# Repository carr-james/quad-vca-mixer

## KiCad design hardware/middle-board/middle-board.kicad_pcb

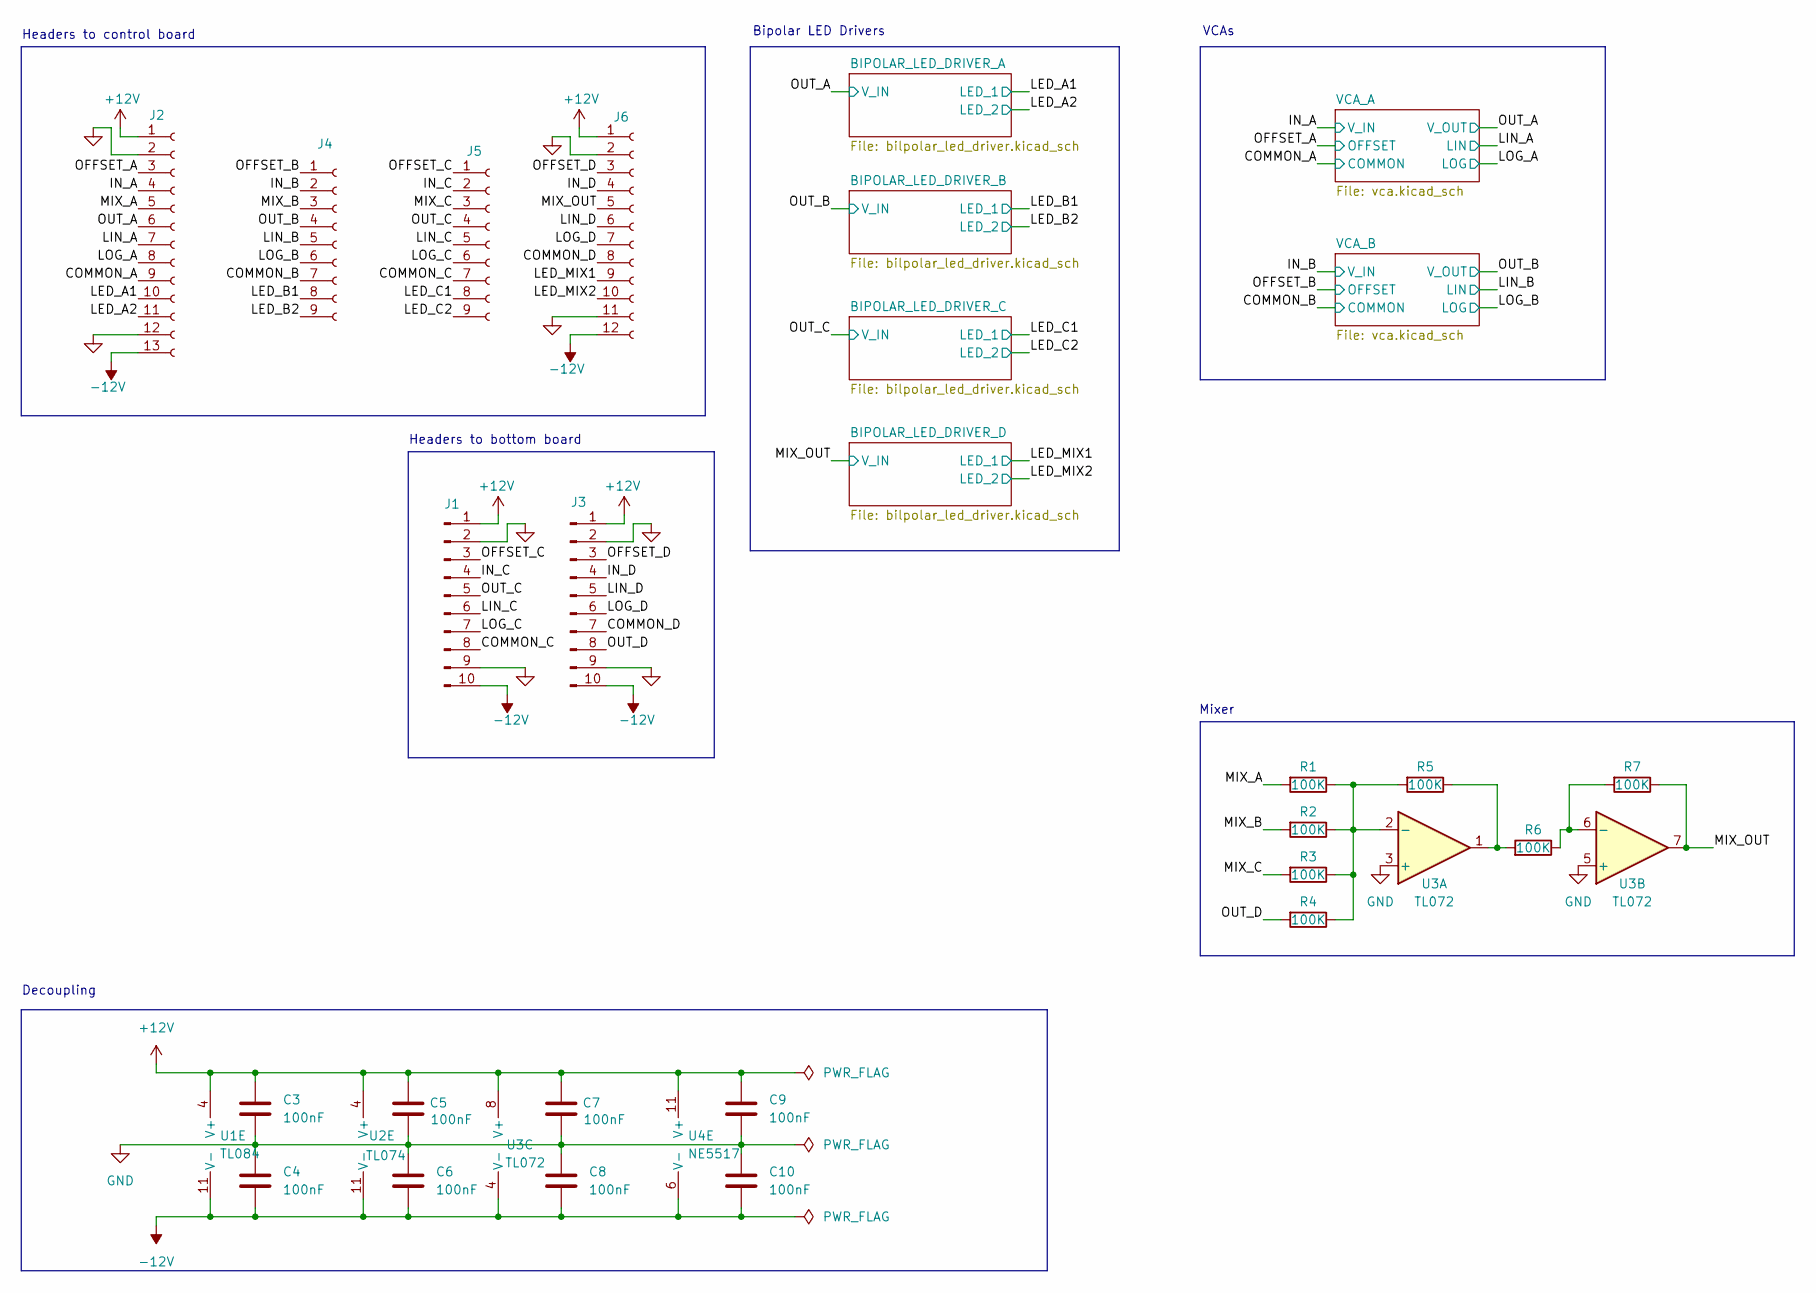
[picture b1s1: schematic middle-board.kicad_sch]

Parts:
C3, C4, C5, C6, C7, C8, C9, C10: 100nF; C_Disc_D3.4mm_W2.1mm_P2.50mm
J1, J3: 01x10 Male Pin Header; PinHeader_1x10_P2.54mm_Vertical
J2: 01x13 Female Pin Header; PinSocket_1x13_P2.54mm_Vertical
J4, J5: 01x09 Female Pin Header; PinSocket_1x09_P2.54mm_Vertical
J6: 01x12 Female Pin Header; PinSocket_1x12_P2.54mm_Vertical
R1, R2, R3, R4, R5, R6, R7: 100K; R_Axial_DIN0207_L6.3mm_D2.5mm_P7.62mm_Horizontal
U1: TL084; Texas_DYY0014A_TSOT-23-14_2x4.2mm_P0.5mm
U2: TL074; DIP-14_W7.62mm
U3: TL072; DIP-8_W7.62mm
U4: NE5517; SOIC-16_3.9x9.9mm_P1.27mm

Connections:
+12V: C3.1, C5.1, C7.1, C9.1, J1.1, J2.1, J3.1, J6.1, U1.4 (V+), U2.4 (V+), U3.8 (V+), U4.11 (V+); also elsewhere on the board
-12V: C4.2, C6.2, C8.2, C10.2, J1.10, J2.13, J3.10, J6.12, U1.11 (V-), U2.11 (V-), U3.4 (V-), U4.6 (V-); also elsewhere on the board
/COMMON_A: J2.9; also elsewhere on the board
/COMMON_B: J4.7, U4.16
/COMMON_C: J1.8, J5.7
/COMMON_D: J3.7, J6.8
/IN_A: J2.4; also elsewhere on the board
/IN_B: J4.2, U4.14 (+); also elsewhere on the board
/IN_C: J1.4, J5.2
/IN_D: J3.4, J6.4
/LED_A1: J2.10, U2.2 (-); also elsewhere on the board
/LED_A2: J2.11, U2.1; also elsewhere on the board
/LED_B1: J4.8, U2.6 (-); also elsewhere on the board
/LED_B2: J4.9, U2.7; also elsewhere on the board
/LED_C1: J5.8; also elsewhere on the board
/LED_C2: J5.9; also elsewhere on the board
/LED_MIX1: J6.9, U2.13 (-); also elsewhere on the board
/LED_MIX2: J6.10, U2.14; also elsewhere on the board
/LIN_A: J2.7; also elsewhere on the board
/LIN_B: J4.5; also elsewhere on the board
/LIN_C: J1.6, J5.5
/LIN_D: J3.5, J6.6
/LOG_A: J2.8; also elsewhere on the board
/LOG_B: J4.6; also elsewhere on the board
/LOG_C: J1.7, J5.6
/LOG_D: J3.6, J6.7
/MIX_A: J2.5, R1.1
/MIX_B: J4.3, R2.1
/MIX_C: J5.3, R3.1
/MIX_OUT: J6.5, R7.2, U2.12 (+), U3.7; also elsewhere on the board
/OFFSET_A: J2.3; also elsewhere on the board
/OFFSET_B: J4.1, U1.9 (-); also elsewhere on the board
/OFFSET_C: J1.3, J5.1
/OFFSET_D: J3.3, J6.3
/OUT_A: J2.6, U2.3 (+); also elsewhere on the board
/OUT_B: J4.4, U2.5 (+), U4.9; also elsewhere on the board
/OUT_C: J1.5, J5.4; also elsewhere on the board
/OUT_D: J3.8, R4.1
GND: C3.2, C4.1, C5.2, C6.1, C7.2, C8.1, C9.2, C10.1, J1.2, J1.9, J2.2, J2.12, J3.2, J3.9, J6.2, J6.11, U3.3 (+), U3.5 (+), U4.13 (-); also elsewhere on the board
unnamed 44: U1.8; also elsewhere on the board
unnamed: R5.2, R6.1, U3.1
unnamed 51: U1.14; also elsewhere on the board
unnamed 53: U4.10, U4.12; also elsewhere on the board
unnamed 57: U1.10 (+); also elsewhere on the board
unnamed 58: U1.12 (+); also elsewhere on the board
unnamed 59: U1.13 (-); also elsewhere on the board
unnamed: R1.2, R2.2, R3.2, R4.2, R5.1, U3.2 (-)
unnamed: R6.2, R7.1, U3.6 (-)

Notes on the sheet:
VCAs
Mixer
Headers to bottom board
Bipolar LED Drivers
Decoupling
Headers to control board

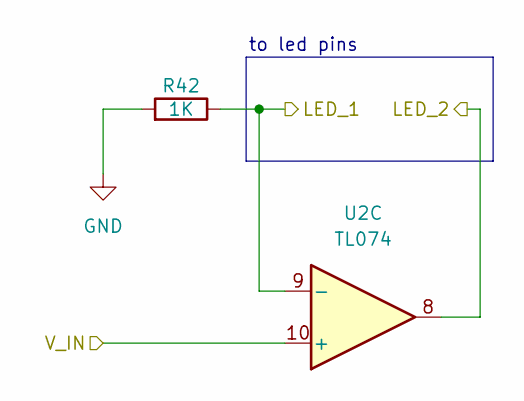
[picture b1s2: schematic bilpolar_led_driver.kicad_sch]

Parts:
R42: 1K; R_Axial_DIN0207_L6.3mm_D2.5mm_P7.62mm_Horizontal
U2: TL074; DIP-14_W7.62mm

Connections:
/LED_A1: U2.2 (-); also elsewhere on the board
/LED_A2: U2.1; also elsewhere on the board
/LED_B1: U2.6 (-); also elsewhere on the board
/LED_B2: U2.7; also elsewhere on the board
/LED_C1: R42.2, U2.9 (-); also elsewhere on the board
/LED_C2: U2.8; also elsewhere on the board
/LED_MIX1: U2.13 (-); also elsewhere on the board
/LED_MIX2: U2.14; also elsewhere on the board
/MIX_OUT: U2.12 (+); also elsewhere on the board
/OUT_A: U2.3 (+); also elsewhere on the board
/OUT_B: U2.5 (+); also elsewhere on the board
/OUT_C: U2.10 (+); also elsewhere on the board
GND: R42.1; also elsewhere on the board

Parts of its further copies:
R40, R41, R43: 1K; R_Axial_DIN0207_L6.3mm_D2.5mm_P7.62mm_Horizontal

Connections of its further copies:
/LED_A1: R40.2; also elsewhere on the board
/LED_B1: R41.2; also elsewhere on the board
/LED_MIX1: R43.2; also elsewhere on the board
GND: R40.1, R41.1, R43.1; also elsewhere on the board

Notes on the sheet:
to led pins

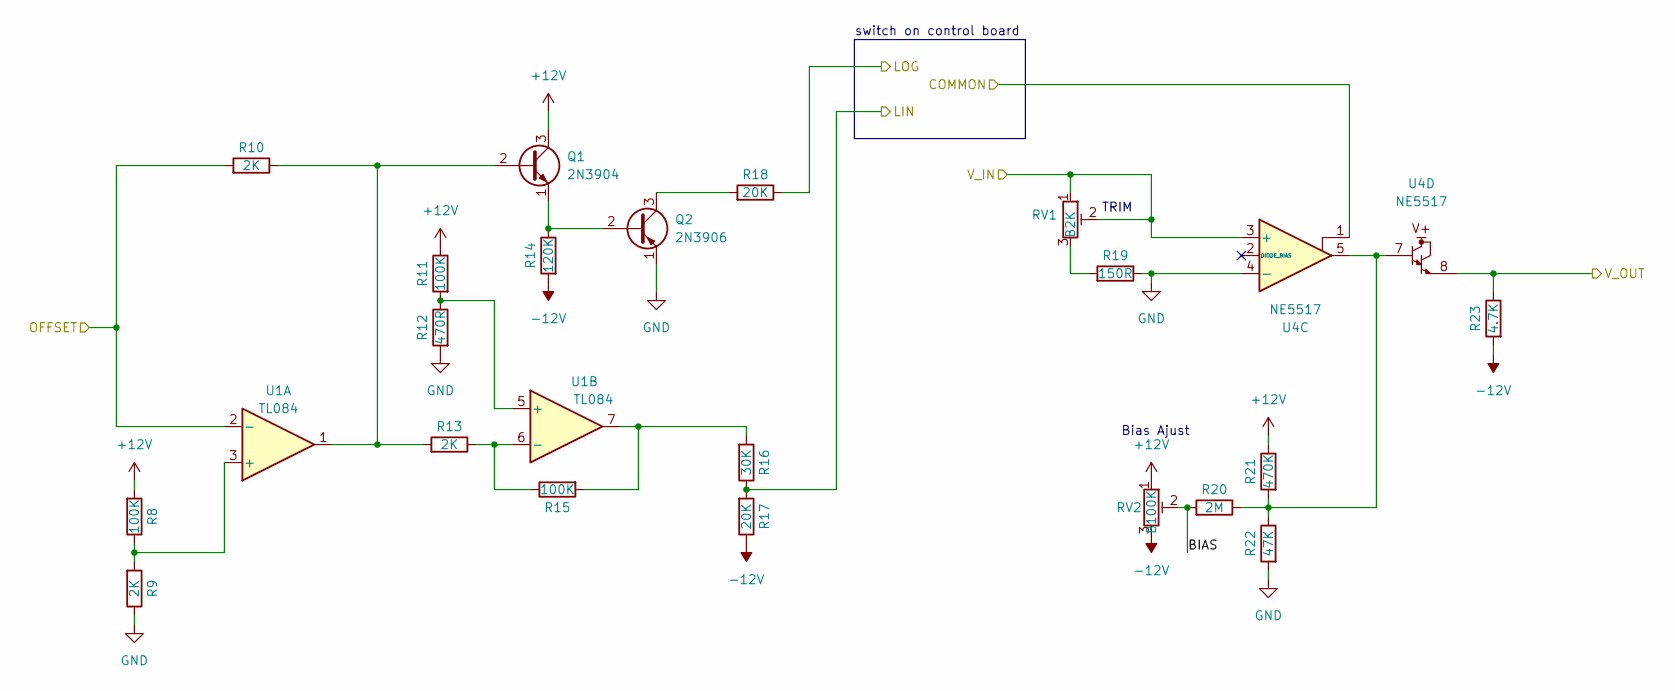
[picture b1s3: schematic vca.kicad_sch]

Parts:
Q1: 2N3904; TO-92_Inline
Q2: 2N3906; TO-92_Inline
R8, R11, R15: 100K; R_Axial_DIN0207_L6.3mm_D2.5mm_P7.62mm_Horizontal
R9, R10, R13: 2K; R_Axial_DIN0207_L6.3mm_D2.5mm_P7.62mm_Horizontal
R12: 470R; R_Axial_DIN0207_L6.3mm_D2.5mm_P7.62mm_Horizontal
R14: 120K; R_Axial_DIN0207_L6.3mm_D2.5mm_P7.62mm_Horizontal
R16: 30K; R_Axial_DIN0207_L6.3mm_D2.5mm_P7.62mm_Horizontal
R17, R18: 20K; R_Axial_DIN0207_L6.3mm_D2.5mm_P7.62mm_Horizontal
R19: 150R; R_Axial_DIN0207_L6.3mm_D2.5mm_P7.62mm_Horizontal
R20: 2M; R_Axial_DIN0207_L6.3mm_D2.5mm_P7.62mm_Horizontal
R21: 470K; R_Axial_DIN0207_L6.3mm_D2.5mm_P7.62mm_Horizontal
R22: 47K; R_Axial_DIN0207_L6.3mm_D2.5mm_P7.62mm_Horizontal
R23: 4.7K; R_Axial_DIN0207_L6.3mm_D2.5mm_P7.62mm_Horizontal
RV1: B2K; Potentiometer_Bourns_3296W_Horizontal
RV2: B100K; Potentiometer_Bourns_3296W_Horizontal
U1: TL084; Texas_DYY0014A_TSOT-23-14_2x4.2mm_P0.5mm
U4: NE5517; SOIC-16_3.9x9.9mm_P1.27mm

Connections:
+12V: Q1.3 (C), R8.1, R11.2, R21.2, RV2.1; also elsewhere on the board
-12V: R14.1, R17.2, R23.1, RV2.3; also elsewhere on the board
/COMMON_A: U4.1; also elsewhere on the board
/COMMON_B: U4.16; also elsewhere on the board
/IN_A: RV1.1, RV1.2, U4.3 (+); also elsewhere on the board
/IN_B: U4.14 (+); also elsewhere on the board
/LIN_A: R16.2, R17.1; also elsewhere on the board
/LOG_A: R18.2; also elsewhere on the board
/OFFSET_A: R10.1, U1.2 (-); also elsewhere on the board
/OFFSET_B: U1.9 (-); also elsewhere on the board
/OUT_A: R23.2, U4.8; also elsewhere on the board
/OUT_B: U4.9; also elsewhere on the board
/VCA_A/BIAS: R20.1, RV2.2
GND: Q2.1 (E), R9.2, R12.1, R19.2, R22.1, U4.4 (-), U4.13 (-); also elsewhere on the board
unnamed 41: Q1.2 (B), R10.2, R13.1, U1.1; also elsewhere on the board
unnamed: Q1.1 (E), Q2.2 (B), R14.2
unnamed: Q2.3 (C), R18.1
unnamed 44: U1.8; also elsewhere on the board
unnamed 48: R15.1, R16.1, U1.7; also elsewhere on the board
unnamed: R19.1, RV1.3
unnamed: R20.2, R21.1, R22.2, U4.5, U4.7
unnamed 51: U1.14; also elsewhere on the board
unnamed 53: U4.10, U4.12; also elsewhere on the board
unnamed 54: R8.2, R9.1, U1.3 (+); also elsewhere on the board
unnamed 55: R11.1, R12.2, U1.5 (+); also elsewhere on the board
unnamed 56: R13.2, R15.2, U1.6 (-); also elsewhere on the board
unnamed 57: U1.10 (+); also elsewhere on the board
unnamed 58: U1.12 (+); also elsewhere on the board
unnamed 59: U1.13 (-); also elsewhere on the board

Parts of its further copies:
Q3: 2N3904; TO-92_Inline
Q4: 2N3906; TO-92_Inline
R24, R27, R31: 100K; R_Axial_DIN0207_L6.3mm_D2.5mm_P7.62mm_Horizontal
R25, R26, R29: 2K; R_Axial_DIN0207_L6.3mm_D2.5mm_P7.62mm_Horizontal
R28: 470R; R_Axial_DIN0207_L6.3mm_D2.5mm_P7.62mm_Horizontal
R30: 120K; R_Axial_DIN0207_L6.3mm_D2.5mm_P7.62mm_Horizontal
R32: 30K; R_Axial_DIN0207_L6.3mm_D2.5mm_P7.62mm_Horizontal
R33, R34: 20K; R_Axial_DIN0207_L6.3mm_D2.5mm_P7.62mm_Horizontal
R35: 150R; R_Axial_DIN0207_L6.3mm_D2.5mm_P7.62mm_Horizontal
R36: 2M; R_Axial_DIN0207_L6.3mm_D2.5mm_P7.62mm_Horizontal
R37: 470K; R_Axial_DIN0207_L6.3mm_D2.5mm_P7.62mm_Horizontal
R38: 47K; R_Axial_DIN0207_L6.3mm_D2.5mm_P7.62mm_Horizontal
R39: 4.7K; R_Axial_DIN0207_L6.3mm_D2.5mm_P7.62mm_Horizontal
RV3: B2K; Potentiometer_Bourns_3296W_Horizontal
RV4: B100K; Potentiometer_Bourns_3296W_Horizontal

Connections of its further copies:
+12V: Q3.3 (C), R24.1, R27.2, R37.2, RV4.1; also elsewhere on the board
-12V: R30.1, R33.2, R39.1, RV4.3; also elsewhere on the board
/IN_B: RV3.1, RV3.2; also elsewhere on the board
/LIN_B: R32.2, R33.1; also elsewhere on the board
/LOG_B: R34.2; also elsewhere on the board
/OFFSET_B: R26.1; also elsewhere on the board
/OUT_B: R39.2; also elsewhere on the board
/VCA_B/BIAS: R36.1, RV4.2
GND: Q4.1 (E), R25.2, R28.1, R35.2, R38.1; also elsewhere on the board
unnamed 44: Q3.2 (B), R26.2, R29.1; also elsewhere on the board
unnamed: Q3.1 (E), Q4.2 (B), R30.2
unnamed: Q4.3 (C), R34.1
unnamed 51: R31.1, R32.1; also elsewhere on the board
unnamed: R35.1, RV3.3
unnamed 53: R36.2, R37.1, R38.2; also elsewhere on the board
unnamed 57: R24.2, R25.1; also elsewhere on the board
unnamed 58: R27.1, R28.2; also elsewhere on the board
unnamed 59: R29.2, R31.2; also elsewhere on the board

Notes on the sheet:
switch on control board
TRIM
Bias Ajust

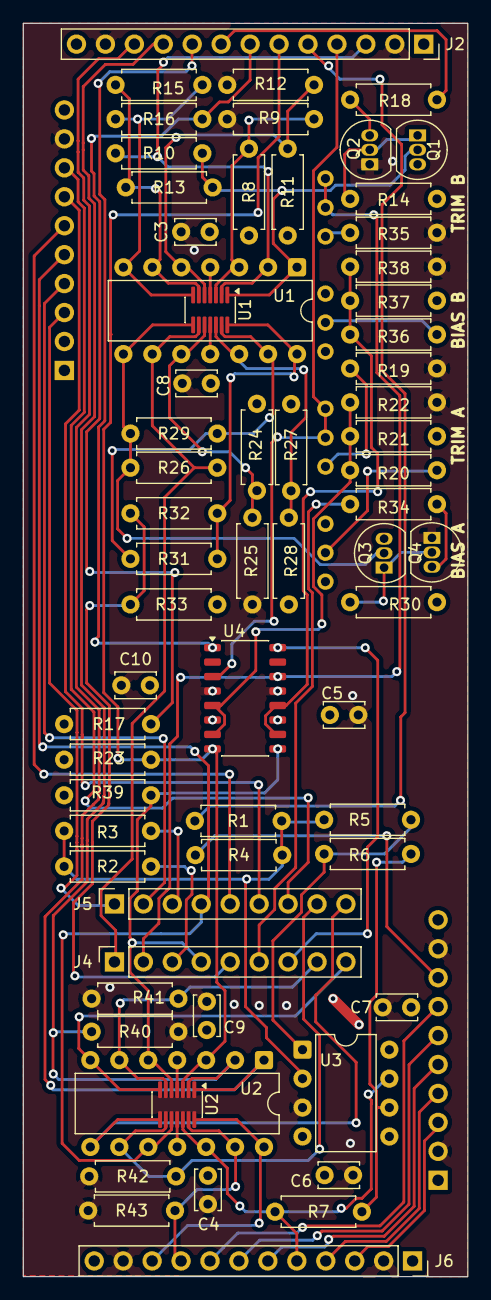
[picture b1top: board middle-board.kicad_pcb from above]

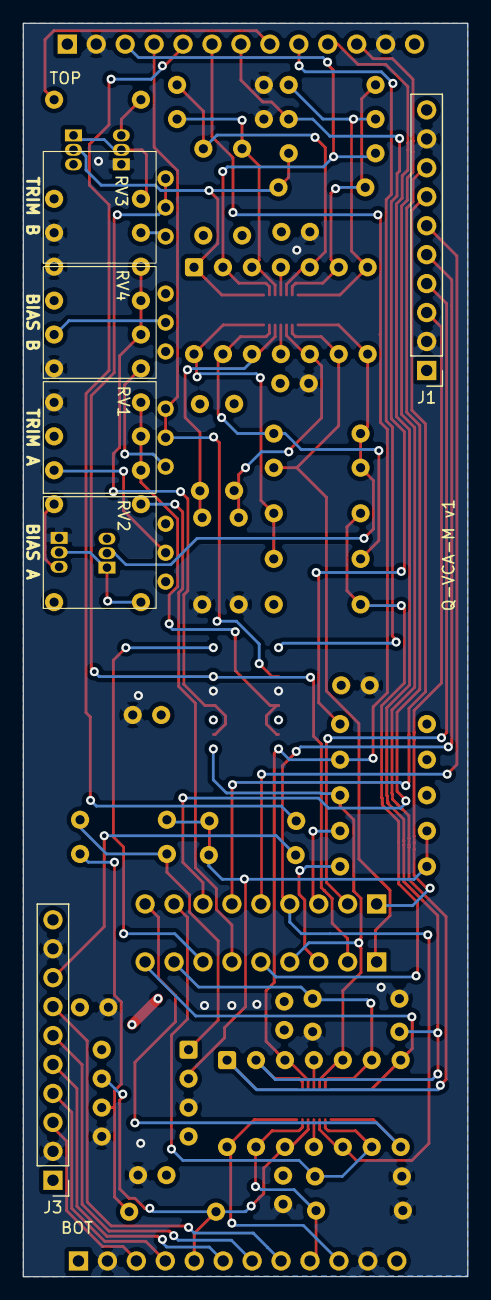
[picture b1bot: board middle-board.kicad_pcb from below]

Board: 4 copper layers, 39.0 x 110.0 mm, 71 parts (6 on the bottom side), 62 nets.

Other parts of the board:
U1#2: TL084; DIP-14_W7.62mm
U2#2: TL074; Texas_DYY0014A_TSOT-23-14_2x4.2mm_P0.5mm

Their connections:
+12V: U1#2.4 (V+), U2#2.4 (V+); also elsewhere on the board
-12V: U1#2.11 (V-), U2#2.11 (V-); also elsewhere on the board
/LED_A1: U2#2.2 (-); also elsewhere on the board
/LED_A2: U2#2.1; also elsewhere on the board
/LED_B1: U2#2.6 (-); also elsewhere on the board
/LED_B2: U2#2.7; also elsewhere on the board
/LED_C1: U2#2.9 (-); also elsewhere on the board
/LED_C2: U2#2.8; also elsewhere on the board
/LED_MIX1: U2#2.13 (-); also elsewhere on the board
/LED_MIX2: U2#2.14; also elsewhere on the board
/MIX_OUT: U2#2.12 (+); also elsewhere on the board
/OFFSET_A: U1#2.2 (-); also elsewhere on the board
/OFFSET_B: U1#2.9 (-); also elsewhere on the board
/OUT_A: U2#2.3 (+); also elsewhere on the board
/OUT_B: U2#2.5 (+); also elsewhere on the board
/OUT_C: U2#2.10 (+); also elsewhere on the board
unnamed 41: U1#2.1; also elsewhere on the board
unnamed 44: U1#2.8; also elsewhere on the board
unnamed 48: U1#2.7; also elsewhere on the board
unnamed 51: U1#2.14; also elsewhere on the board
unnamed 54: U1#2.3 (+); also elsewhere on the board
unnamed 55: U1#2.5 (+); also elsewhere on the board
unnamed 56: U1#2.6 (-); also elsewhere on the board
unnamed 57: U1#2.10 (+); also elsewhere on the board
unnamed 58: U1#2.12 (+); also elsewhere on the board
unnamed 59: U1#2.13 (-); also elsewhere on the board

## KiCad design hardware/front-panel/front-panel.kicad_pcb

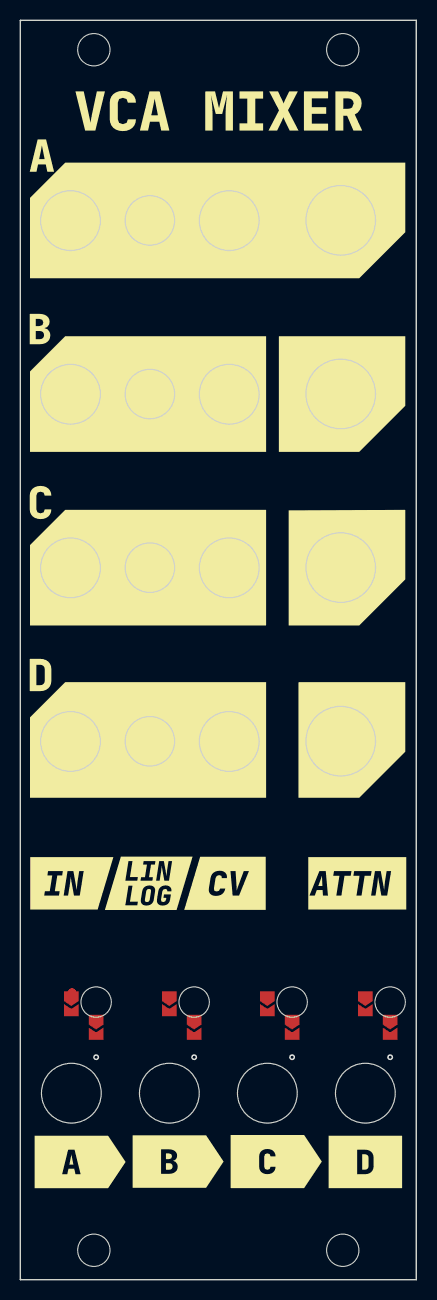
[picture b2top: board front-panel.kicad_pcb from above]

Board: 2 copper layers, 40.4 x 128.5 mm, 45 parts (0 on the bottom side), 4 nets.

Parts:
D1, D2, D3, D4: Bipolar LED; LED_D3.0mm_FP
J1, J2, J3, J4, J5, J6, J7, J8, J13, J14, J15, J16: Thonkicon; Thonkicon_FP
JP1, JP1#2, JP2, JP2#2, JP3, JP3#2, JP4, JP4#2: Jumper_2_Small_Bridged; SolderJumper-2_P1.3mm_Open_TrianglePad1.0x1.5mm
RV1, RV2, RV3, RV4: A100K; Alpha Potentiometer_FP
SW1, SW2, SW3, SW4: Subminiture SPDT; Sub-Miniature SPDT_FP
kibuzzard-690A2C8E: G***; kibuzzard-690A2C8E
kibuzzard-690A16BA: G***; kibuzzard-690A16BA
kibuzzard-690A26A7: G***; kibuzzard-690A26A7
kibuzzard-690A27E8: G***; kibuzzard-690A27E8
kibuzzard-690A27F2: G***; kibuzzard-690A27F2
kibuzzard-690A27FD: G***; kibuzzard-690A27FD
kibuzzard-690A058A: G***; kibuzzard-690A058A
kibuzzard-690A0571: G***; kibuzzard-690A0571
kibuzzard-690A0582: G***; kibuzzard-690A0582
kibuzzard-690A0592: G***; kibuzzard-690A0592
kibuzzard-690A1385: G***; kibuzzard-690A1385
kibuzzard-690A2811: G***; kibuzzard-690A2811
kibuzzard-69095FA6: G***; kibuzzard-69095FA6

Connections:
/DUMMY_NET_A: JP1.1 (A), JP1#2.1 (A)
/DUMMY_NET_B: JP2.1 (A), JP2#2.1 (A)
unnamed: JP1.2 (B), JP1#2.2 (B), JP3.1 (A), JP3#2.1 (A)
unnamed: JP2.2 (B), JP2#2.2 (B), JP4.1 (A), JP4#2.1 (A)

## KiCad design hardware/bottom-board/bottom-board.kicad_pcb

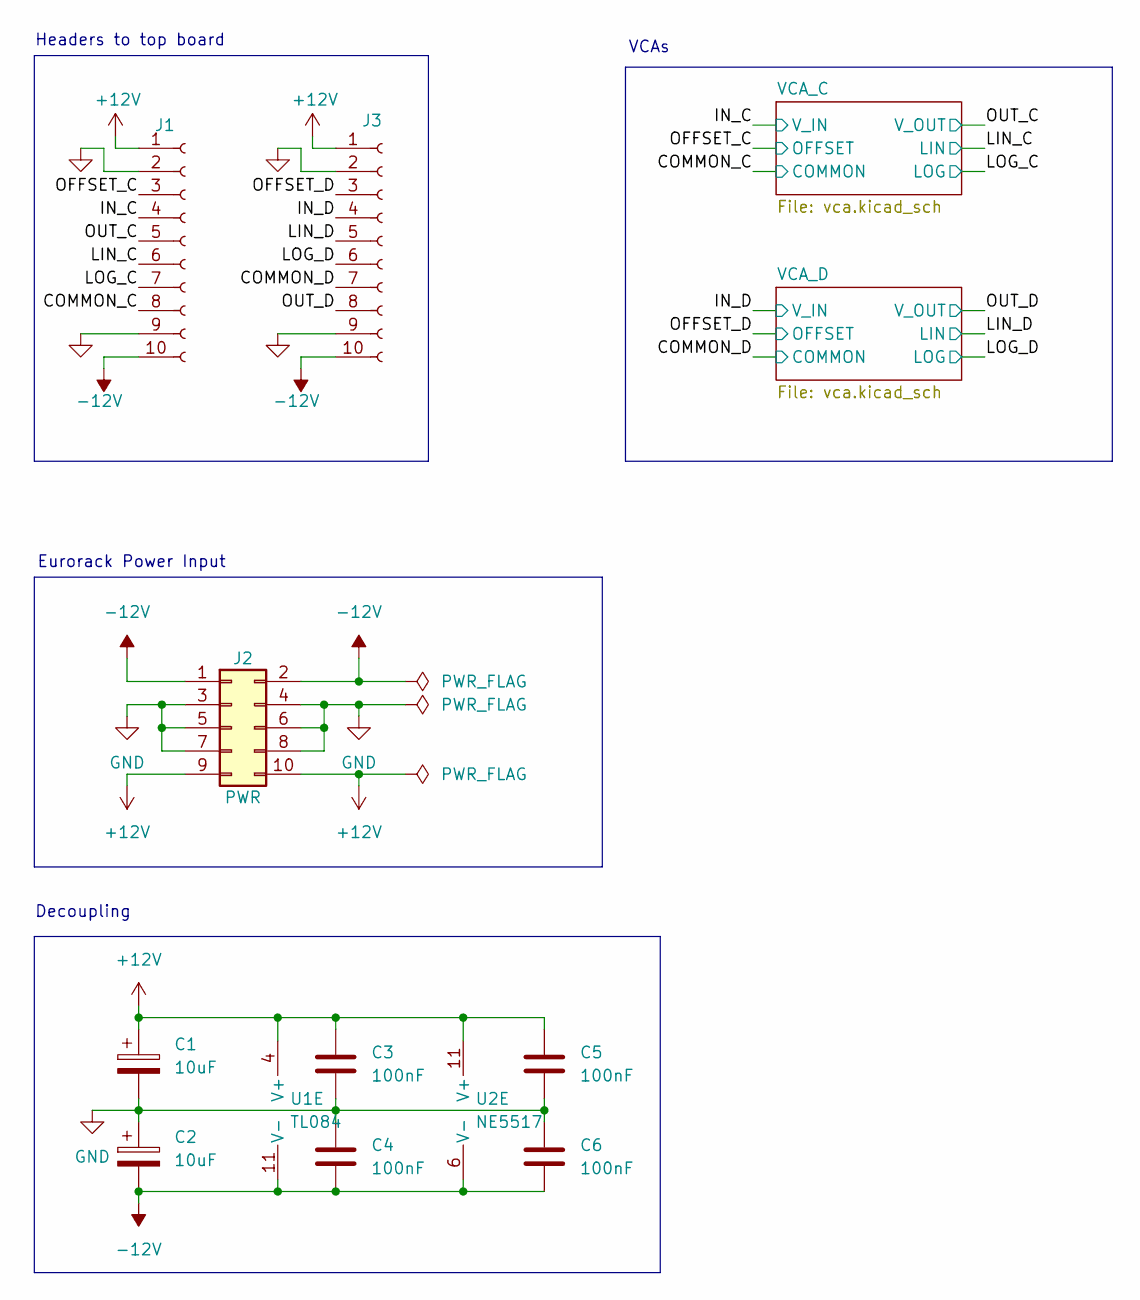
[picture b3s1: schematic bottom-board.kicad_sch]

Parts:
C1, C2: 10uF; CP_Radial_D5.0mm_H11.0mm_P2.00mm
C3, C4, C5, C6: 100nF; C_Disc_D3.4mm_W2.1mm_P2.50mm
J1, J3: 01x10 Female Pin Header; PinSocket_1x10_P2.54mm_Vertical
J2: PWR; Eurorack Power Header (10 pin)
U1: TL084; Texas_DYY0014A_TSOT-23-14_2x4.2mm_P0.5mm
U2: NE5517; SOIC-16_3.9x9.9mm_P1.27mm

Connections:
+12V: C1.1, C3.1, C5.1, J1.1, J2.9, J2.10, J3.1, U1.4 (V+), U2.11 (V+); also elsewhere on the board
-12V: C2.2, C4.2, C6.2, J1.10, J2.1, J2.2, J3.10, U1.11 (V-), U2.6 (V-); also elsewhere on the board
/COMMON_C: J1.8; also elsewhere on the board
/COMMON_D: J3.7, U2.1
/IN_C: J1.4; also elsewhere on the board
/IN_D: J3.4, U2.3 (+); also elsewhere on the board
/LIN_C: J1.6; also elsewhere on the board
/LIN_D: J3.5; also elsewhere on the board
/LOG_C: J1.7; also elsewhere on the board
/LOG_D: J3.6; also elsewhere on the board
/OFFSET_C: J1.3; also elsewhere on the board
/OFFSET_D: J3.3, U1.9 (-); also elsewhere on the board
/OUT_C: J1.5; also elsewhere on the board
/OUT_D: J3.8, U2.8; also elsewhere on the board
GND: C1.2, C2.1, C3.2, C4.1, C5.2, C6.1, J1.2, J1.9, J2.3, J2.4, J2.5, J2.6, J2.7, J2.8, J3.2, J3.9, U2.4 (-); also elsewhere on the board
unnamed 20: U1.8; also elsewhere on the board
unnamed 26: U1.14; also elsewhere on the board
unnamed 28: U2.5, U2.7; also elsewhere on the board
unnamed 32: U1.10 (+); also elsewhere on the board
unnamed 33: U1.12 (+); also elsewhere on the board
unnamed 34: U1.13 (-); also elsewhere on the board

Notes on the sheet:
Headers to top board
Eurorack Power Input
VCAs
Decoupling

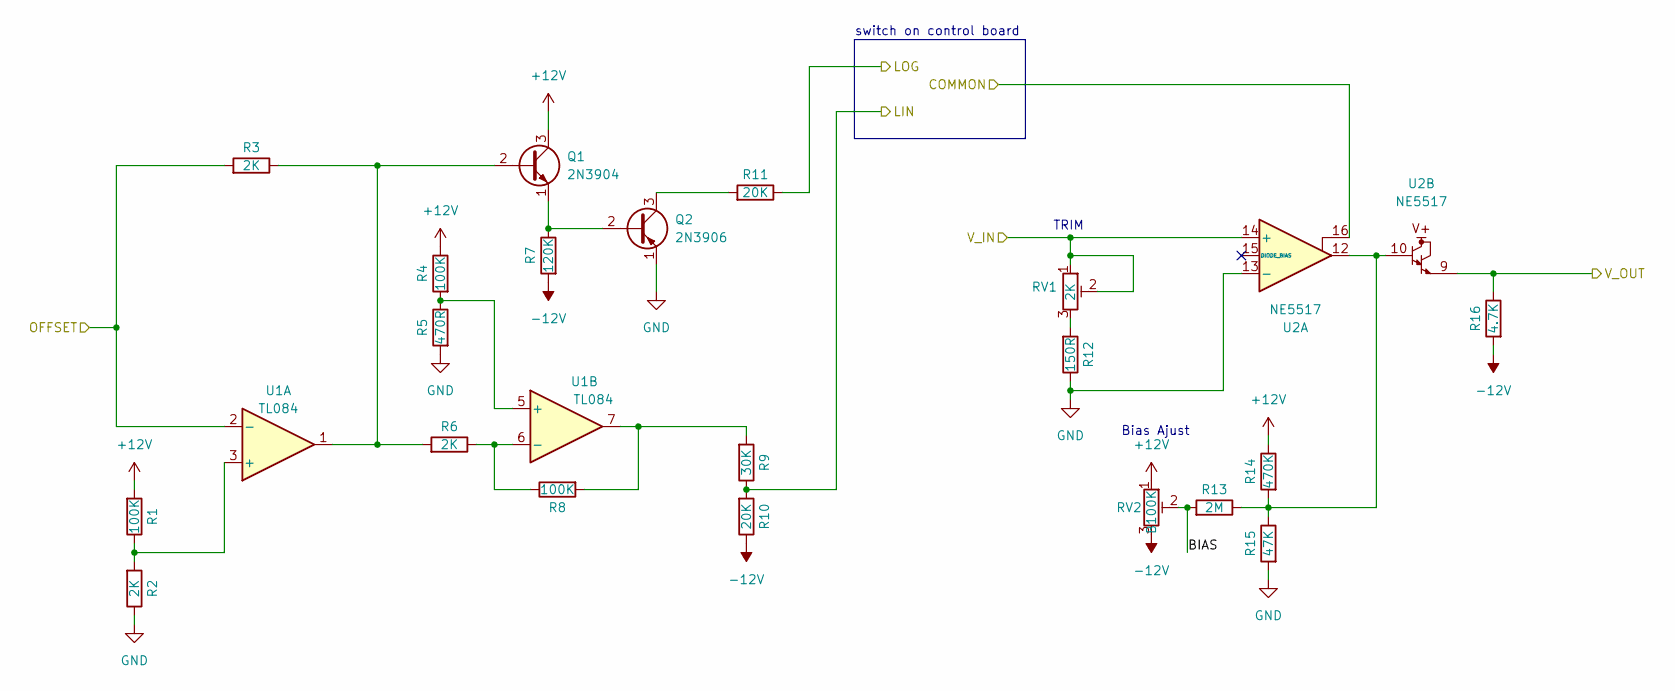
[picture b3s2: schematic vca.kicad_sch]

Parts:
Q1: 2N3904; TO-92_Inline
Q2: 2N3906; TO-92_Inline
R1, R4, R8: 100K; R_Axial_DIN0207_L6.3mm_D2.5mm_P7.62mm_Horizontal
R2, R3, R6: 2K; R_Axial_DIN0207_L6.3mm_D2.5mm_P7.62mm_Horizontal
R5: 470R; R_Axial_DIN0207_L6.3mm_D2.5mm_P7.62mm_Horizontal
R7: 120K; R_Axial_DIN0207_L6.3mm_D2.5mm_P7.62mm_Horizontal
R9: 30K; R_Axial_DIN0207_L6.3mm_D2.5mm_P7.62mm_Horizontal
R10, R11: 20K; R_Axial_DIN0207_L6.3mm_D2.5mm_P7.62mm_Horizontal
R12: 150R; R_Axial_DIN0207_L6.3mm_D2.5mm_P7.62mm_Horizontal
R13: 2M; R_Axial_DIN0207_L6.3mm_D2.5mm_P7.62mm_Horizontal
R14: 470K; R_Axial_DIN0207_L6.3mm_D2.5mm_P7.62mm_Horizontal
R15: 47K; R_Axial_DIN0207_L6.3mm_D2.5mm_P7.62mm_Horizontal
R16: 4.7K; R_Axial_DIN0207_L6.3mm_D2.5mm_P7.62mm_Horizontal
RV1: 2K; Potentiometer_Bourns_3296W_Horizontal
RV2: B100K; Potentiometer_Bourns_3296W_Horizontal
U1: TL084; Texas_DYY0014A_TSOT-23-14_2x4.2mm_P0.5mm
U2: NE5517; SOIC-16_3.9x9.9mm_P1.27mm

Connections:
+12V: Q1.3 (C), R1.1, R4.2, R14.2, RV2.1; also elsewhere on the board
-12V: R7.1, R10.2, R16.1, RV2.3; also elsewhere on the board
/COMMON_C: U2.16; also elsewhere on the board
/COMMON_D: U2.1; also elsewhere on the board
/IN_C: RV1.1, RV1.2, U2.14 (+); also elsewhere on the board
/IN_D: U2.3 (+); also elsewhere on the board
/LIN_C: R9.2, R10.1; also elsewhere on the board
/LOG_C: R11.2; also elsewhere on the board
/OFFSET_C: R3.1, U1.2 (-); also elsewhere on the board
/OFFSET_D: U1.9 (-); also elsewhere on the board
/OUT_C: R16.2, U2.9; also elsewhere on the board
/OUT_D: U2.8; also elsewhere on the board
/VCA_C/BIAS: R13.1, RV2.2
GND: Q2.1 (E), R2.2, R5.1, R12.2, R15.1, U2.4 (-), U2.13 (-); also elsewhere on the board
unnamed 17: Q1.2 (B), R3.2, R6.1, U1.1; also elsewhere on the board
unnamed: Q1.1 (E), Q2.2 (B), R7.2
unnamed: Q2.3 (C), R11.1
unnamed 20: U1.8; also elsewhere on the board
unnamed 23: R8.1, R9.1, U1.7; also elsewhere on the board
unnamed: R12.1, RV1.3
unnamed: R13.2, R14.1, R15.2, U2.10, U2.12
unnamed 26: U1.14; also elsewhere on the board
unnamed 28: U2.5, U2.7; also elsewhere on the board
unnamed 29: R1.2, R2.1, U1.3 (+); also elsewhere on the board
unnamed 30: R4.1, R5.2, U1.5 (+); also elsewhere on the board
unnamed 31: R6.2, R8.2, U1.6 (-); also elsewhere on the board
unnamed 32: U1.10 (+); also elsewhere on the board
unnamed 33: U1.12 (+); also elsewhere on the board
unnamed 34: U1.13 (-); also elsewhere on the board

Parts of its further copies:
Q3: 2N3904; TO-92_Inline
Q4: 2N3906; TO-92_Inline
R17, R20, R24: 100K; R_Axial_DIN0207_L6.3mm_D2.5mm_P7.62mm_Horizontal
R18, R19, R22: 2K; R_Axial_DIN0207_L6.3mm_D2.5mm_P7.62mm_Horizontal
R21: 470R; R_Axial_DIN0207_L6.3mm_D2.5mm_P7.62mm_Horizontal
R23: 120K; R_Axial_DIN0207_L6.3mm_D2.5mm_P7.62mm_Horizontal
R25: 30K; R_Axial_DIN0207_L6.3mm_D2.5mm_P7.62mm_Horizontal
R26, R27: 20K; R_Axial_DIN0207_L6.3mm_D2.5mm_P7.62mm_Horizontal
R28: 150R; R_Axial_DIN0207_L6.3mm_D2.5mm_P7.62mm_Horizontal
R29: 2M; R_Axial_DIN0207_L6.3mm_D2.5mm_P7.62mm_Horizontal
R30: 470K; R_Axial_DIN0207_L6.3mm_D2.5mm_P7.62mm_Horizontal
R31: 47K; R_Axial_DIN0207_L6.3mm_D2.5mm_P7.62mm_Horizontal
R32: 4.7K; R_Axial_DIN0207_L6.3mm_D2.5mm_P7.62mm_Horizontal
RV3: 2K; Potentiometer_Bourns_3296W_Horizontal
RV4: B100K; Potentiometer_Bourns_3296W_Horizontal

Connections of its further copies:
+12V: Q3.3 (C), R17.1, R20.2, R30.2, RV4.1; also elsewhere on the board
-12V: R23.1, R26.2, R32.1, RV4.3; also elsewhere on the board
/IN_D: RV3.1, RV3.2; also elsewhere on the board
/LIN_D: R25.2, R26.1; also elsewhere on the board
/LOG_D: R27.2; also elsewhere on the board
/OFFSET_D: R19.1; also elsewhere on the board
/OUT_D: R32.2; also elsewhere on the board
/VCA_D/BIAS: R29.1, RV4.2
GND: Q4.1 (E), R18.2, R21.1, R28.2, R31.1; also elsewhere on the board
unnamed 20: Q3.2 (B), R19.2, R22.1; also elsewhere on the board
unnamed: Q3.1 (E), Q4.2 (B), R23.2
unnamed: Q4.3 (C), R27.1
unnamed 26: R24.1, R25.1; also elsewhere on the board
unnamed: R28.1, RV3.3
unnamed 28: R29.2, R30.1, R31.2; also elsewhere on the board
unnamed 32: R17.2, R18.1; also elsewhere on the board
unnamed 33: R20.1, R21.2; also elsewhere on the board
unnamed 34: R22.2, R24.2; also elsewhere on the board

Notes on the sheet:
switch on control board
Bias Ajust
TRIM

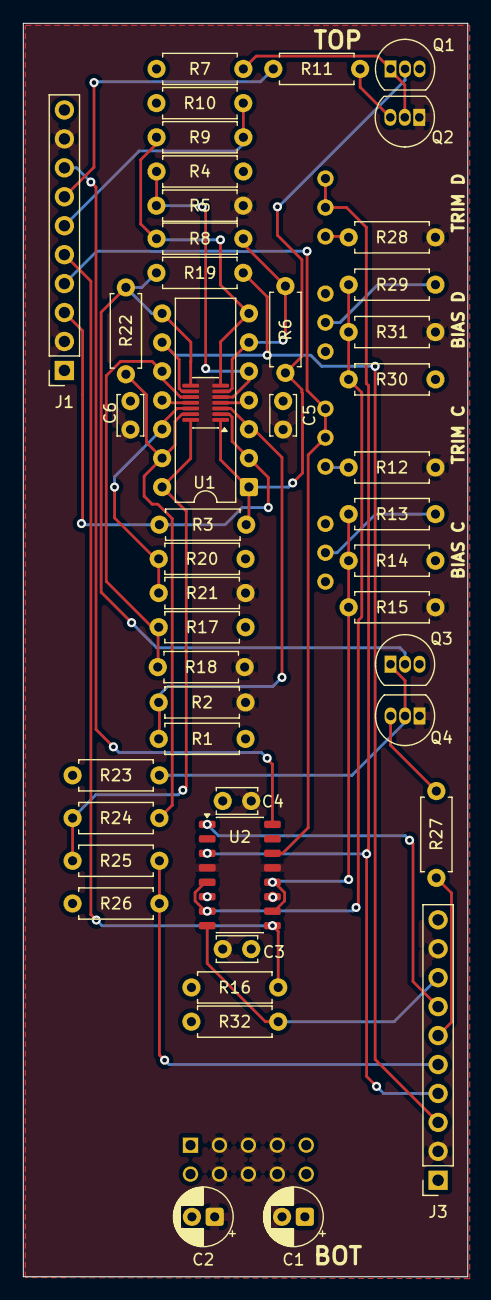
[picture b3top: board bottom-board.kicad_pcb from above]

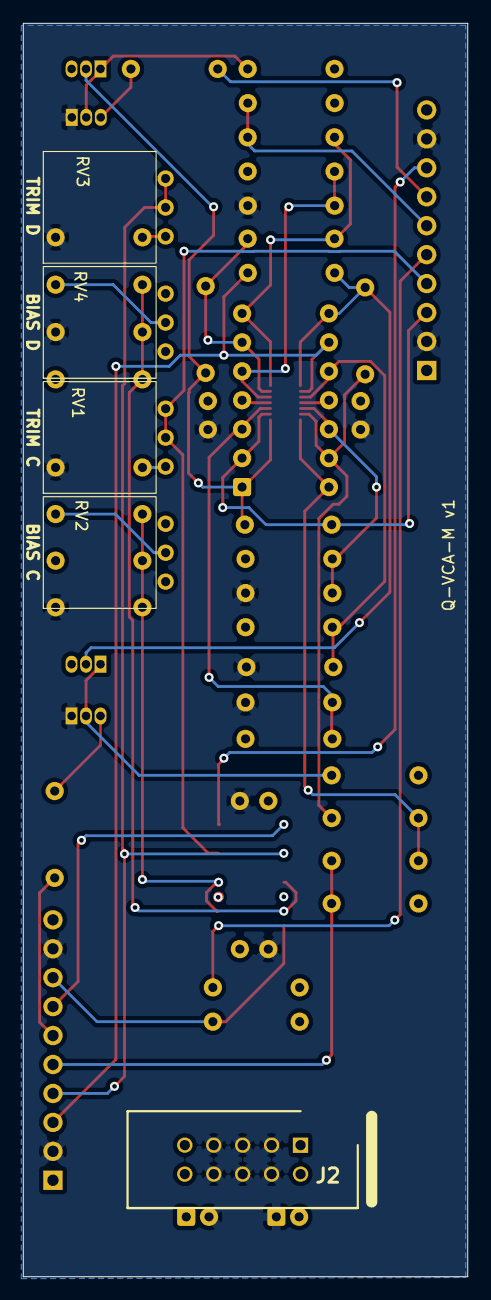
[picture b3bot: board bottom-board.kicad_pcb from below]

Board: 4 copper layers, 39.0 x 110.0 mm, 52 parts (5 on the bottom side), 35 nets.

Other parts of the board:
U1#2: TL084; Texas_DYY0014A_TSOT-23-14_2x4.2mm_P0.5mm

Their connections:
+12V: U1#2.4 (V+); also elsewhere on the board
-12V: U1#2.11 (V-); also elsewhere on the board
/OFFSET_C: U1#2.2 (-); also elsewhere on the board
/OFFSET_D: U1#2.9 (-); also elsewhere on the board
unnamed 17: U1#2.1; also elsewhere on the board
unnamed 20: U1#2.8; also elsewhere on the board
unnamed 23: U1#2.7; also elsewhere on the board
unnamed 26: U1#2.14; also elsewhere on the board
unnamed 29: U1#2.3 (+); also elsewhere on the board
unnamed 30: U1#2.5 (+); also elsewhere on the board
unnamed 31: U1#2.6 (-); also elsewhere on the board
unnamed 32: U1#2.10 (+); also elsewhere on the board
unnamed 33: U1#2.12 (+); also elsewhere on the board
unnamed 34: U1#2.13 (-); also elsewhere on the board
